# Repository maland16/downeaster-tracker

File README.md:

# downeaster-tracker
A ESP-32 based train tracker for the Amtrak Downeaster
# Inspiration
This project was inspired by the [TrainTrackr line of PCB based LED live train maps](https://www.traintrackr.io/). The PCB design is a mishmash of [their open source board design](https://github.com/Traintrackr/board_files) as well as various [ESP-32 PCB design youtube videos](https://www.youtube.com/watch?v=jiJGbWOSdMo) and online resources. 

# A footnote on the HT16K33
I have a mixed review of this LED driver. On one hand, its age and extensive use in the DIY electronics space means it has pretty robust support. On the other hand, it's old. I wasn't able to source any from the usual suspects (digikey, mouser, etc.) and resorted to picking some up on Ebay. The kicad footprint and symbol are in /PCB. Also, despite the datasheet saying otherwise, it seems as though it can run just fine at 3.3V, and is used extensively in production designs at that voltage.

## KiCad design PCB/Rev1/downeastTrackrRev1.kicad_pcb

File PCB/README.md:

## Issues with Rev0
- Boot pin isn't connected to anything :(
-

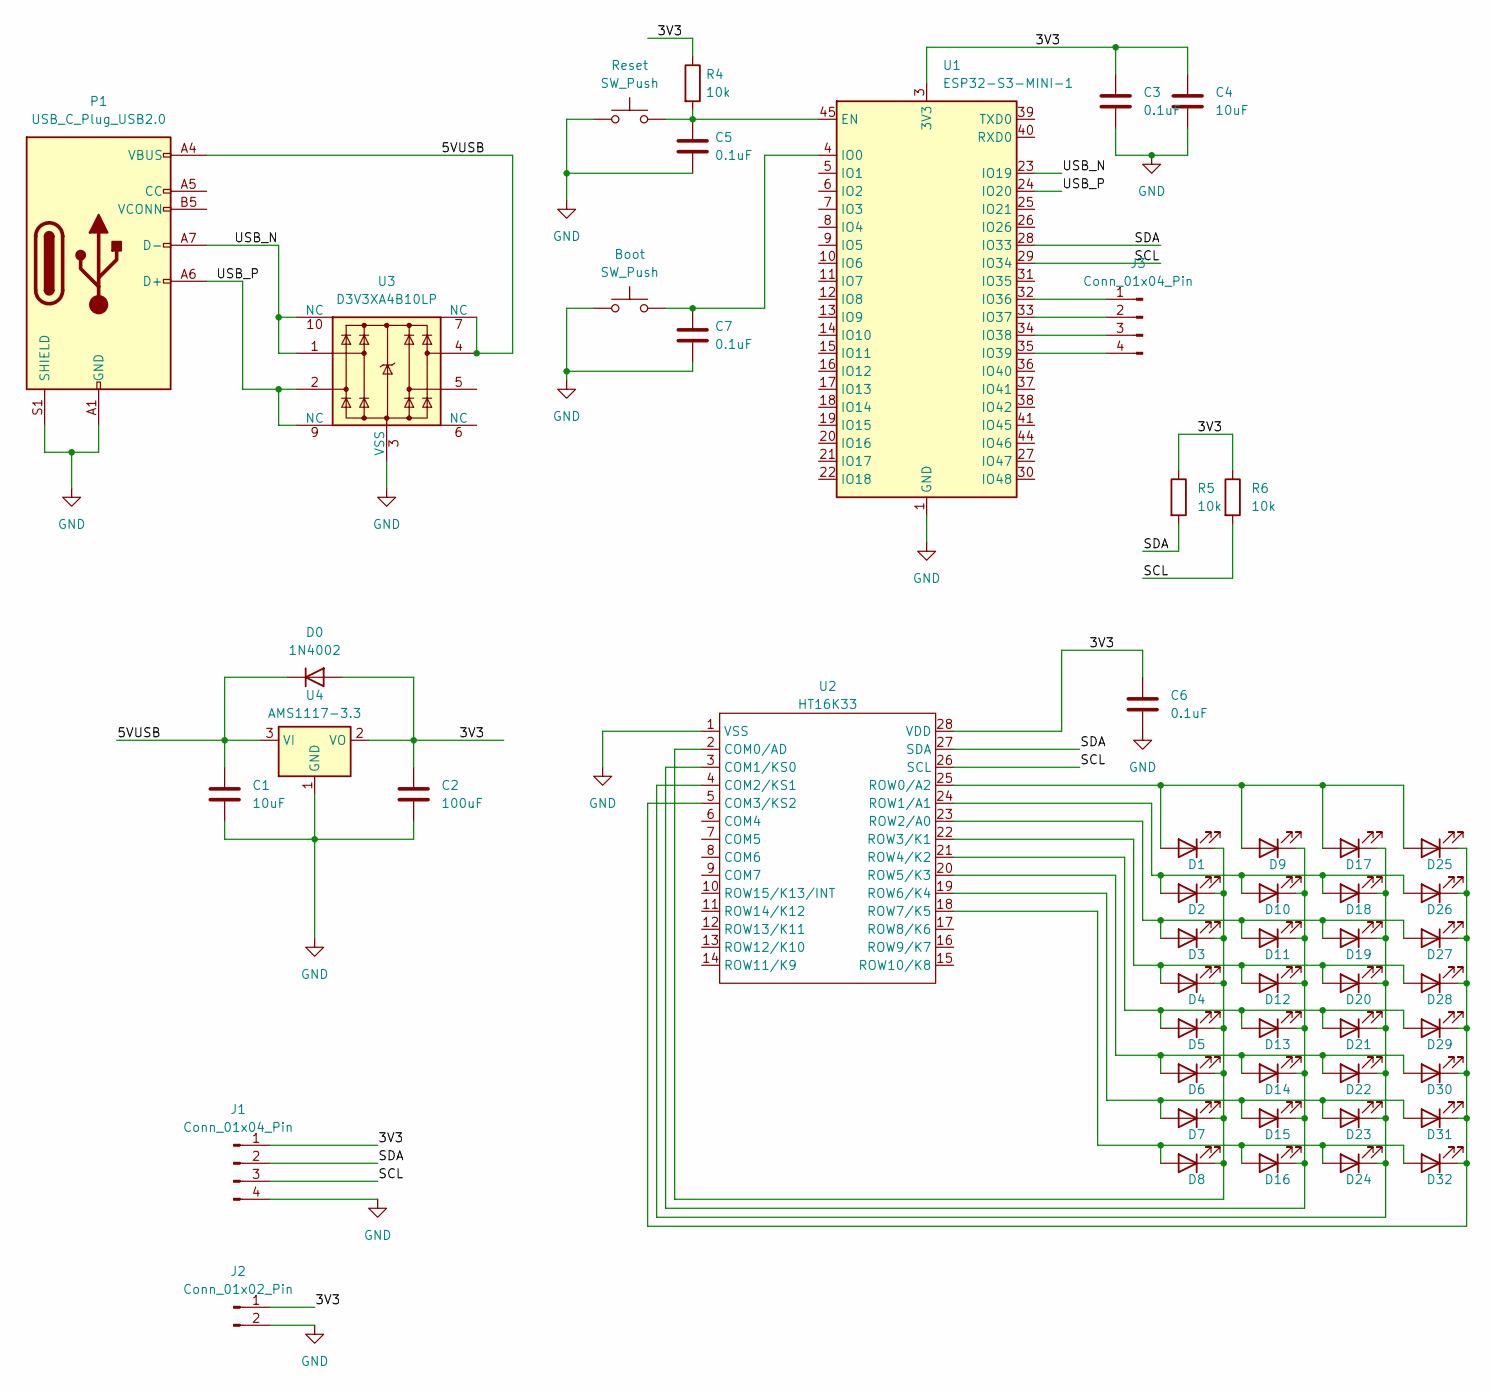
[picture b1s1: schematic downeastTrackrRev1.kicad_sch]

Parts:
Boot: SW_Push; SW_PUSH_6mm
C1, C4: 10uF; CP_Radial_D5.0mm_P2.00mm
C2: 100uF; CP_Radial_D5.0mm_P2.00mm
C3, C5, C6, C7: 0.1uF; C_0805_2012Metric_Pad1.18x1.45mm_HandSolder; LCSC C28233
D0: 1N4002; D_DO-41_SOD81_P10.16mm_Horizontal
D1, D2, D3, D4, D5, D6, D7, D8, D9, D10, D11, D12, D13, D14, D15, D16: LED; LED_0805_2012Metric; LCSC C84259
D17, D18, D19, D20, D21, D22, D23, D24, D25, D26, D27, D28, D29, D30, D31, D32: LED; LED_0805_2012Metric; LCSC C84260
J1, J3: Conn_01x04_Pin; PinHeader_1x04_P1.27mm_Vertical
J2: Conn_01x02_Pin; PinHeader_1x02_P2.54mm_Vertical
P1: USB_C_Plug_USB2.0; USB_C_Receptacle_HRO_TYPE-C-31-M-12; LCSC C165948
R4, R5, R6: 10k; R_0805_2012Metric_Pad1.20x1.40mm_HandSolder; LCSC C17414
Reset: SW_Push; SW_PUSH_6mm
U1: ESP32-S3-MINI-1; ESP32-S2-MINI-1; LCSC C2913206
U2: HT16K33; HT16K33_SOP28
U3: D3V3XA4B10LP; Diodes_UDFN-10_1.0x2.5mm_P0.5mm; LCSC C1980462
U4: AMS1117-3.3; SOT-223-3_TabPin2; LCSC C6186

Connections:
/3V3: C2.1, C3.1, C4.1, C6.1, D0.2 (A), J1.1, J2.1, R4.1, R5.1, R6.1, U1.3 (3V3), U2.28 (VDD), U4.2 (VO)
/5VUSB: C1.1, D0.1 (K), P1.A4 (VBUS), P1.A9 (VBUS), P1.B4 (VBUS), P1.B9 (VBUS), U3.4, U3.7 (NC), U4.3 (VI)
/SCL: J1.3, R6.2, U1.29 (IO34), U2.26 (SCL)
/SDA: J1.2, R5.2, U1.28 (IO33), U2.27 (SDA)
/USB_N: P1.A7 (D-), U1.23 (IO19), U3.1, U3.10 (NC)
/USB_P: P1.A6 (D+), U1.24 (IO20), U3.2, U3.9 (NC)
GND: Boot.1, C1.2, C2.2, C3.2, C4.2, C5.2, C6.2, C7.2, J1.4, J2.2, P1.A1 (GND), P1.A12 (GND), P1.B1 (GND), P1.B12 (GND), P1.S1 (SHIELD), Reset.1, U1.1 (GND), U1.2 (GND), U1.42 (GND), U1.43 (GND), U1.46 (GND), U1.47 (GND), U1.48 (GND), U1.49 (GND), U1.50 (GND), U1.51 (GND), U1.52 (GND), U1.53 (GND), U1.54 (GND), U1.55 (GND), U1.56 (GND), U1.57 (GND), U1.58 (GND), U1.59 (GND), U1.60 (GND), U1.61 (GND), U1.62 (GND), U1.63 (GND), U1.64 (GND), U1.65 (GND), U2.1 (VSS), U3.3 (VSS), U3.8 (VSS), U4.1 (GND); also elsewhere on the board
unnamed: Boot.2, C7.1, U1.4 (IO0)
unnamed: D1.2 (A), D9.2 (A), D17.2 (A), D25.2 (A), U2.25 (ROW0/A2)
unnamed: D1.1 (K), D2.1 (K), D3.1 (K), D4.1 (K), D5.1 (K), D6.1 (K), D7.1 (K), D8.1 (K), U2.2 (COM0/AD)
unnamed: D2.2 (A), D10.2 (A), D18.2 (A), D26.2 (A), U2.24 (ROW1/A1)
unnamed: D9.1 (K), D10.1 (K), D11.1 (K), D12.1 (K), D13.1 (K), D14.1 (K), D15.1 (K), D16.1 (K), U2.3 (COM1/KS0)
unnamed: D3.2 (A), D11.2 (A), D19.2 (A), D27.2 (A), U2.23 (ROW2/A0)
unnamed: D4.2 (A), D12.2 (A), D20.2 (A), D28.2 (A), U2.22 (ROW3/K1)
unnamed: D5.2 (A), D13.2 (A), D21.2 (A), D29.2 (A), U2.21 (ROW4/K2)
unnamed: D6.2 (A), D14.2 (A), D22.2 (A), D30.2 (A), U2.20 (ROW5/K3)
unnamed: D7.2 (A), D15.2 (A), D23.2 (A), D31.2 (A), U2.19 (ROW6/K4)
unnamed: D8.2 (A), D16.2 (A), D24.2 (A), D32.2 (A), U2.18 (ROW7/K5)
unnamed: D17.1 (K), D18.1 (K), D19.1 (K), D20.1 (K), D21.1 (K), D22.1 (K), D23.1 (K), D24.1 (K), U2.4 (COM2/KS1)
unnamed: D25.1 (K), D26.1 (K), D27.1 (K), D28.1 (K), D29.1 (K), D30.1 (K), D31.1 (K), D32.1 (K), U2.5 (COM3/KS2)
unnamed: J3.1, U1.32 (IO36)
unnamed: J3.2, U1.33 (IO37)
unnamed: J3.3, U1.34 (IO38)
unnamed: J3.4, U1.35 (IO39)
unnamed 24: C5.1, R4.2, Reset.2, U1.45 (EN); also elsewhere on the board

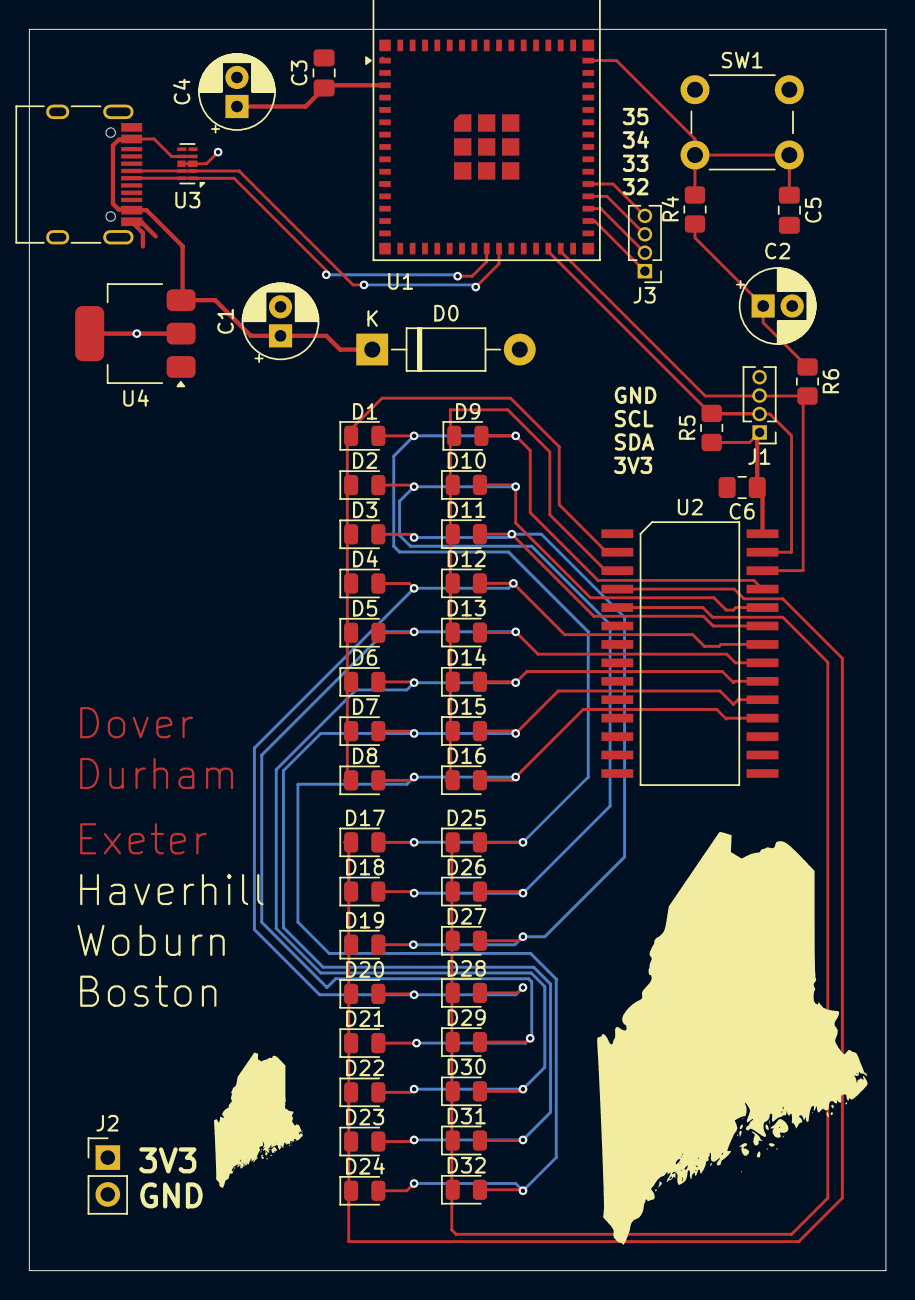
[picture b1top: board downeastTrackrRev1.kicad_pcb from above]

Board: 4 copper layers, 59.0 x 85.5 mm, 51 parts (0 on the bottom side), 24 nets.

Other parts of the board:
SW1: SW_Push; SW_PUSH_6mm

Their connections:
GND: SW1.1; also elsewhere on the board
unnamed 24: SW1.2; also elsewhere on the board

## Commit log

2025-01-13 test script & rev0 PCB
2025-01-16 PythonParsingTest: Polished up & added station coords
2025-01-16 Rev1: Started work on rev1
2025-01-16 PCB: Added HT16K33 driver resources
